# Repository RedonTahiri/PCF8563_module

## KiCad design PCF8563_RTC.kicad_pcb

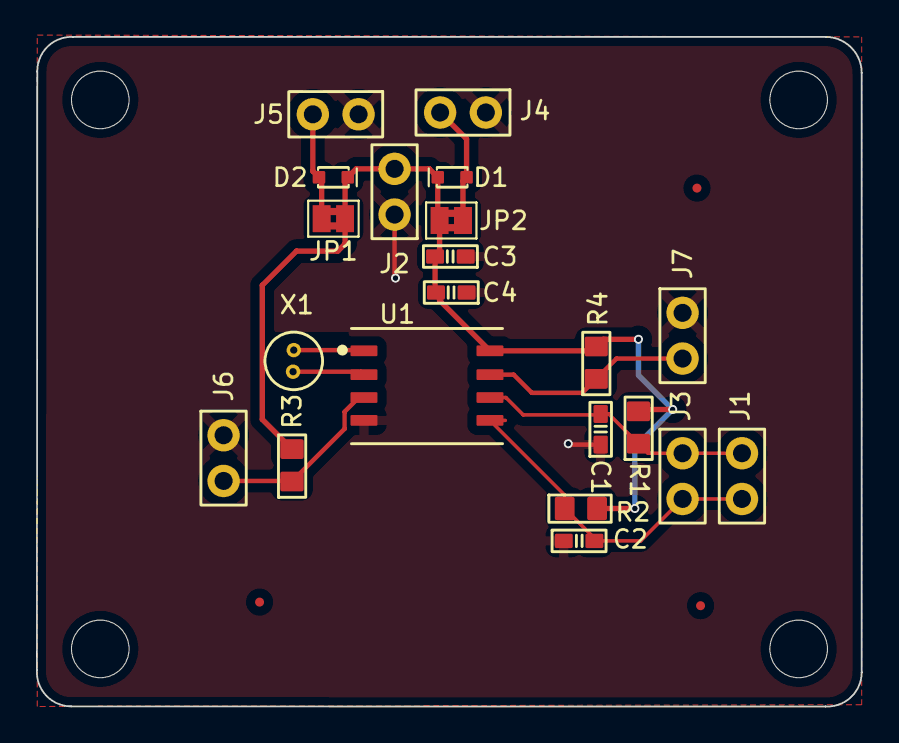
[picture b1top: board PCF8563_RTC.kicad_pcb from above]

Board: 2 copper layers, 45.8 x 37.2 mm, 28 parts (0 on the bottom side), 10 nets.

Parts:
C1, C2: 10pF 1%; C0603
C3, C4: 100nF; C0603
D1, D2: D; D0603
FID1, FID2, FID3: Fiducial; Fiducial_0.5mm_Mask1.5mm
H1, H2, H3, H4: MountingHole_Pad; MountingHole_3.2mm_M3
J1, J2, J3, J4, J5, J6, J7: CONN_2P
JP1, JP2: SolderJumper_2_Open; SolderJumper-2_P1.3mm_Bridged2Bar_Pad1.0x1.5mm
R1, R2, R3, R4: 2.2k; R0603
U1: PCF8563; PCF8563_SO8
X1: 32.768 kHz; CRYSTAL_DT38

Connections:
+5V: D1.1, J4.1, JP2.2 (B)
+BATT: D2.1, J5.1, JP1.2 (B)
/CLKI: U1.1 (CLKI), X1.1
/CLKO: U1.2 (CLKO), X1.2
/CLKOUT: J7.1, R4.1, U1.7 (CLKOUT)
/I2C_SCL: C1.2, J1.2, J3.2, R1.1, U1.6 (SCK)
/I2C_SDA: C2.2, J1.1, J3.1, R2.1, U1.5 (SDA)
/~INT: J6.1, R3.1, U1.3 (~INT)
GND: C1.1, C2.1, C3.1, C4.1, J2.2, J4.2, J5.2, J6.2, J7.2, U1.4 (VSS)
VDD: C3.2, C4.2, D1.2, D2.2, J2.1, JP1.1 (A), JP2.1 (A), R1.2, R2.2, R3.2, R4.2, U1.8 (VDD)

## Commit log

2022-03-28 First push
2022-03-30 Created footprints for the PCF8563-SO8 package and capacitors
2022-04-07 Finished PCB layout and routing
2022-04-15 Finished PCB Layout
